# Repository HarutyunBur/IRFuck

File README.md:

Hello this is my first hack project i made it on Kicad but also i want to upgrade it , make 3d printed corpus for it and make firmware for this module

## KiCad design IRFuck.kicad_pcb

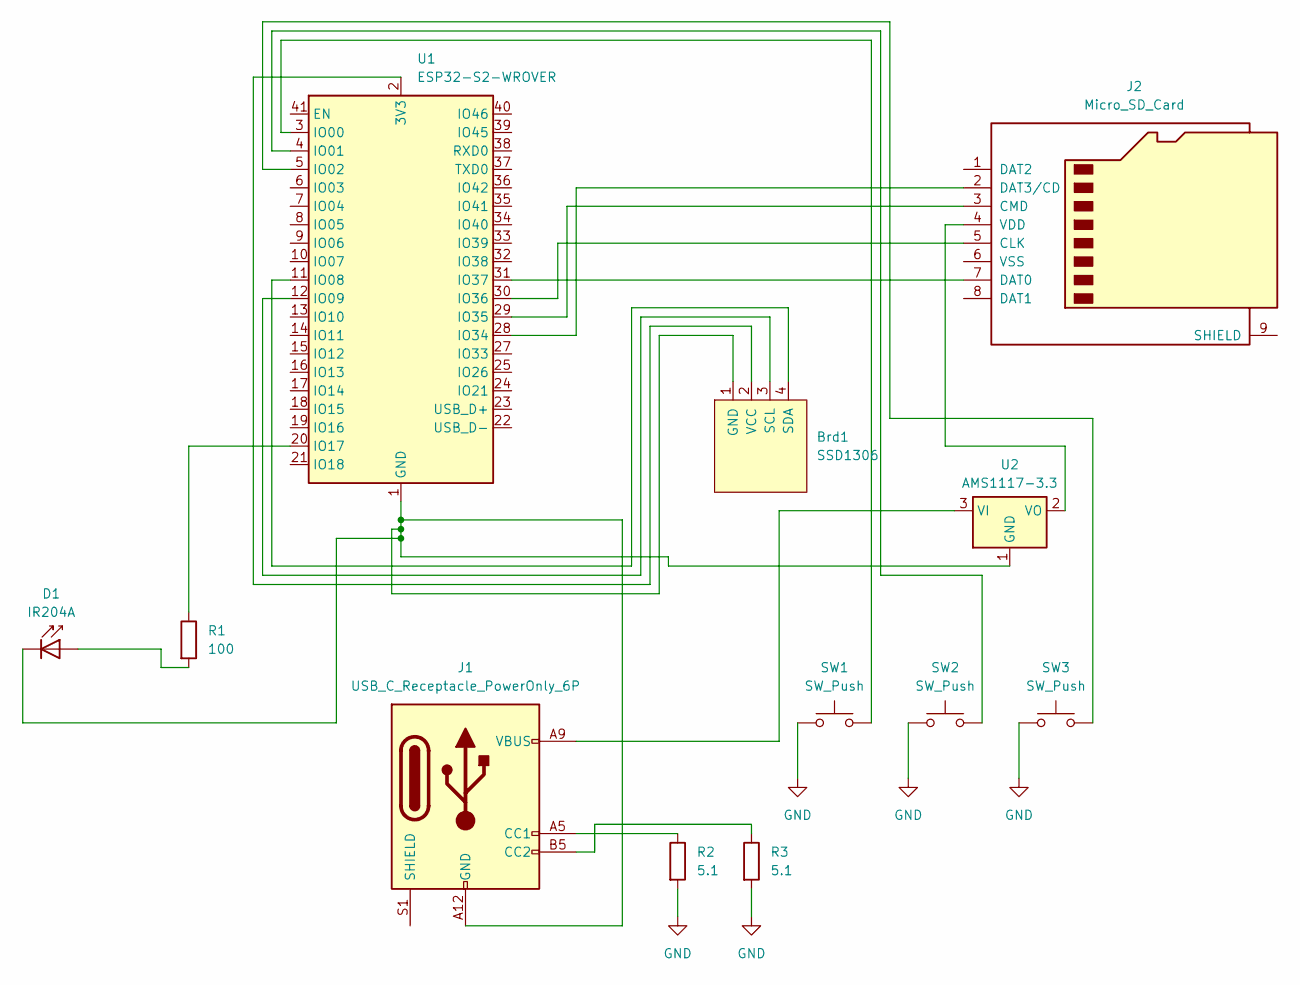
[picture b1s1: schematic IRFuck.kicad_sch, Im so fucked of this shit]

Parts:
Brd1: SSD1306; Adafruit_SSD1306
D1: IR204A; LED_D5.0mm
J1: USB_C_Receptacle_PowerOnly_6P; USB_C_Receptacle_HRO_TYPE-C-31-M-12
J2: Micro_SD_Card; microSD_HC_Hirose_DM3AT-SF-PEJM5
R1: 100; R_0603_1608Metric
R2, R3: 5.1; R_0603_1608Metric
SW1, SW2, SW3: SW_Push; SW_SPST_TL3342
U1: ESP32-S2-WROVER
U2: AMS1117-3.3; SOT-223

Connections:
GND: R2.2, R3.2, SW1.1, SW2.1, SW3.1
unnamed: Brd1.1 (GND), D1.1 (K), J1.A12 (GND), J1.B12 (GND), U1.1 (GND), U1.26 (GND), U1.42 (GND), U1.43 (GND), U2.1 (GND)
unnamed: Brd1.3 (SCL), U1.12 (IO09)
unnamed: Brd1.4 (SDA), U1.11 (IO08)
unnamed: Brd1.2 (VCC), U1.2 (3V3)
unnamed: D1.2 (A), R1.2
unnamed: J1.A5 (CC1), R2.1
unnamed: J1.B5 (CC2), R3.1
unnamed: J2.5 (CLK), U1.30 (IO36)
unnamed: J2.3 (CMD), U1.29 (IO35)
unnamed: J2.7 (DAT0), U1.31 (IO37)
unnamed: J2.2 (DAT3/CD), U1.28 (IO34)
unnamed: J2.4 (VDD), U2.2 (VO)
unnamed: SW1.2, U1.3 (IO00)
unnamed: SW2.2, U1.4 (IO01)
unnamed: SW3.2, U1.5 (IO02)
unnamed: R1.1, U1.20 (IO17)
unnamed: J1.A9 (VBUS), J1.B9 (VBUS), U2.3 (VI)

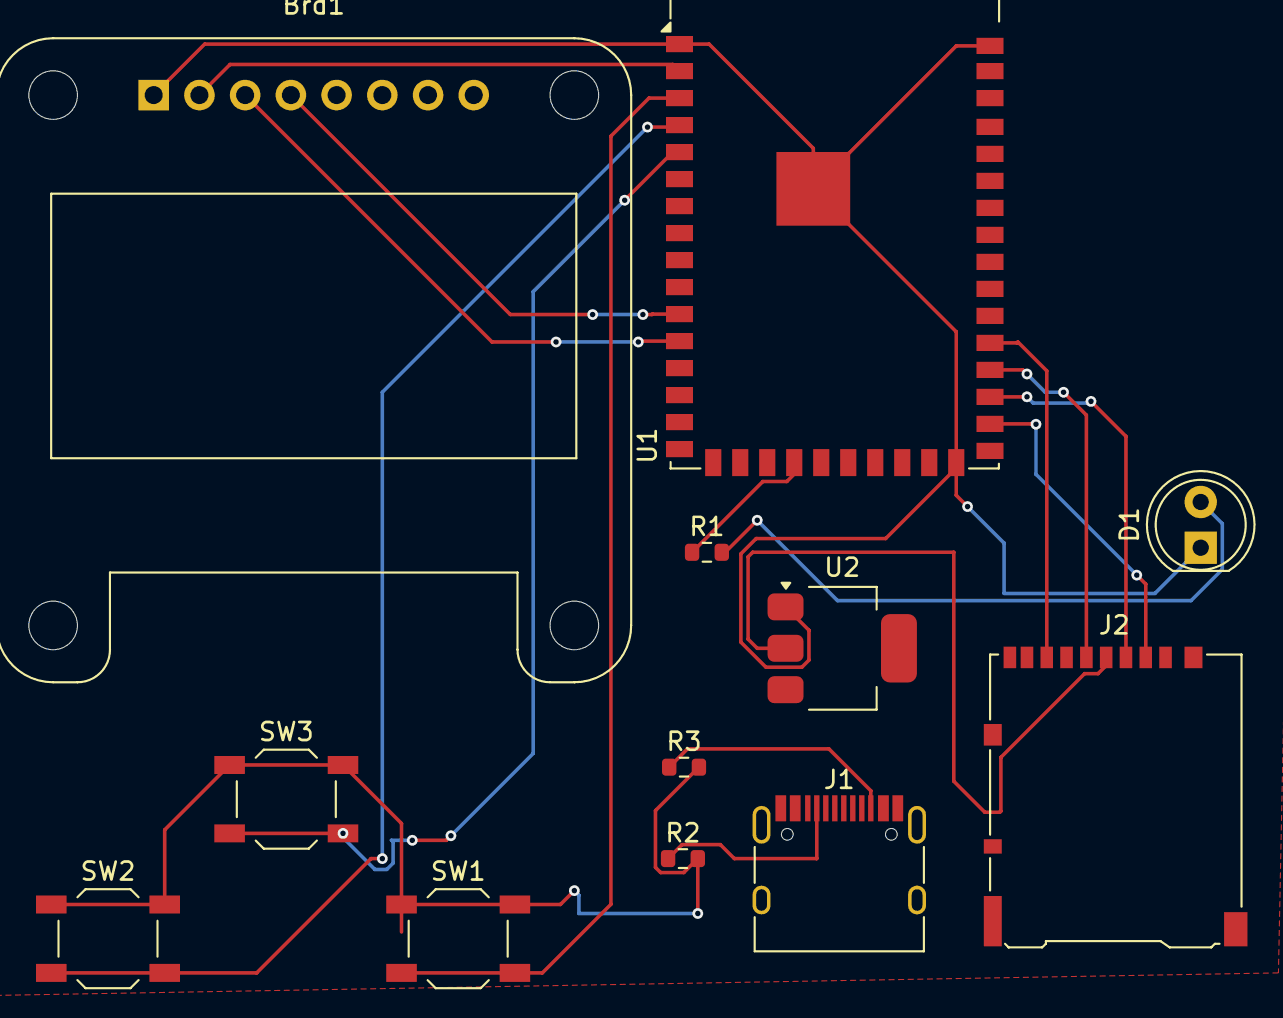
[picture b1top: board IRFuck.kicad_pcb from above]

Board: 2 copper layers, 12 parts (0 on the bottom side), 18 nets.

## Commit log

2025-04-30 Create README.md
    Pls like it
2025-04-30 This is a Kicad file with pcb that i don't finish
    Pls if you can upgrade this pcb pls upgrade and send me a message
